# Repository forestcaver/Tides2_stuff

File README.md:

# Tides2_stuff
Panel, modified pcb to put the recom on the back, calibration stuff
(pcb and panel both verified - two modules built 11/4/19)

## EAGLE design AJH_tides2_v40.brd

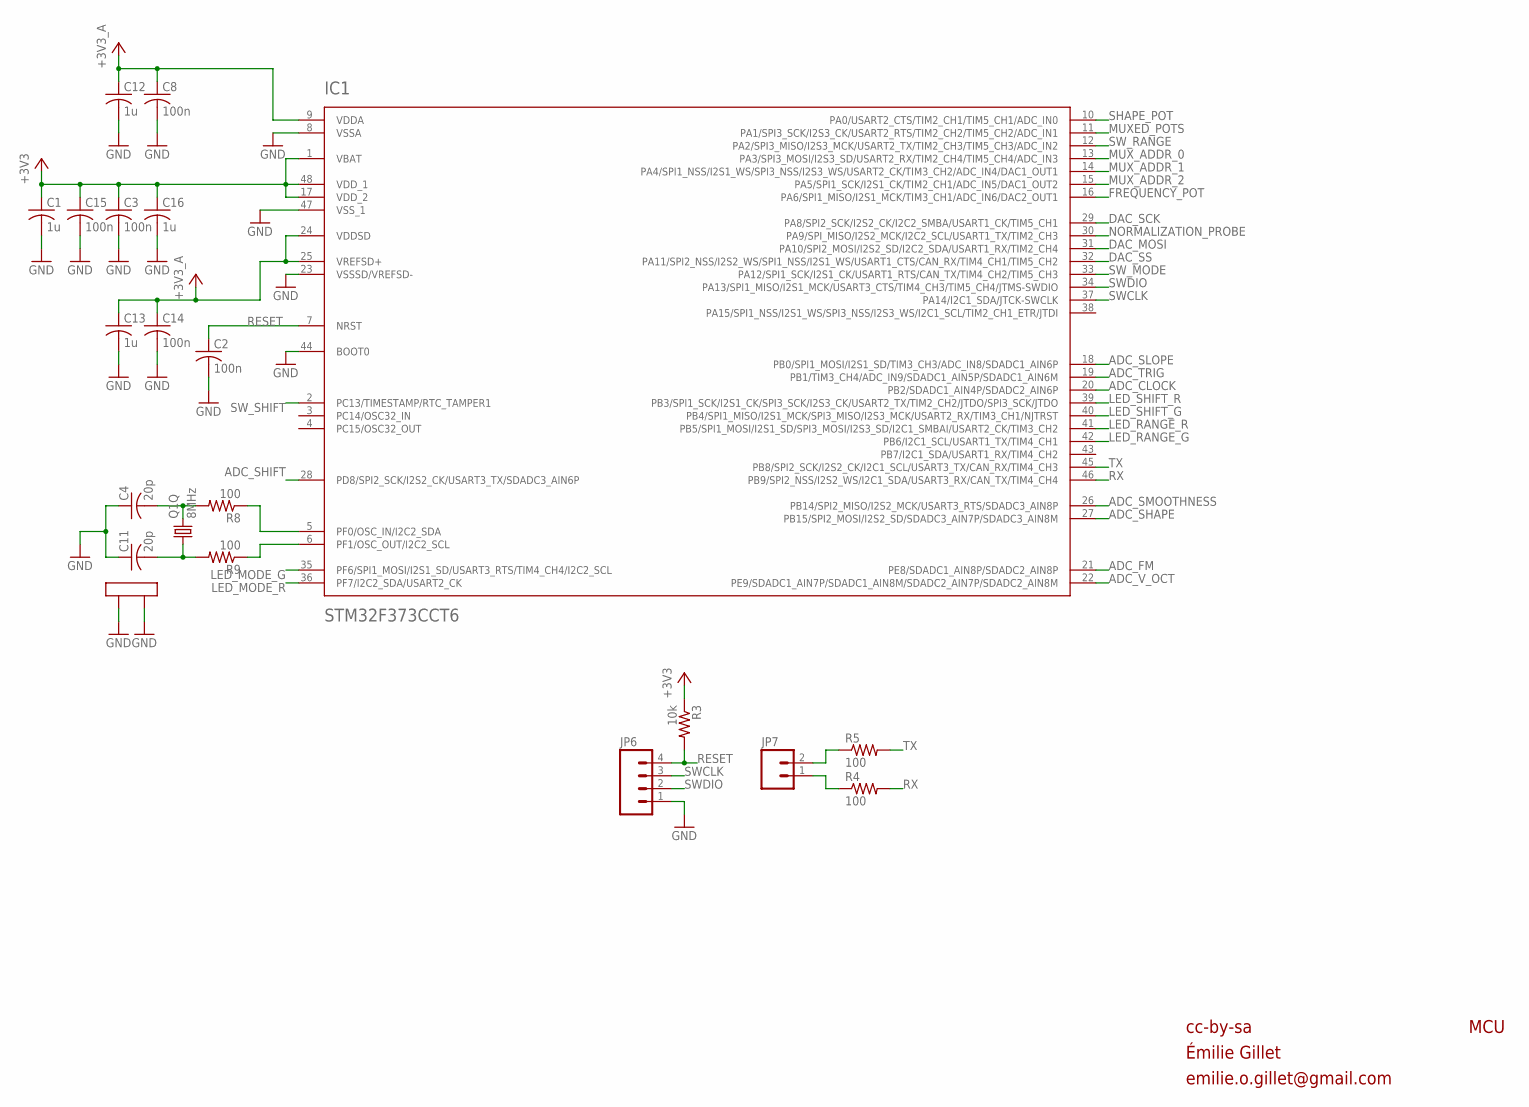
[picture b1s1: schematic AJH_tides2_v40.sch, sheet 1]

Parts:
C1, C12, C13, C16: 1u; C0402
C2, C3, C8, C14, C15: 100n; C0402
C4, C11: 20p; C0402
IC1: STM32F373CCT6; LQFP48
JP6: M04PTH; 1X04
JP7: M02PTH; 1X02
Q1: 8MHz; CTS406
R3: 10k; R0402
R4, R5, R8, R9: 100; R0402

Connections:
+3V3: C1.1, C3.1, C15.1, C16.1, IC1.1 (VBAT), IC1.17 (VDD_2), IC1.48 (VDD_1), R3.1; also elsewhere on the board
+3V3_A: C8.1, C12.1, C13.1, C14.1, IC1.9 (VDDA), IC1.24 (VDDSD), IC1.25 (VREFSD+); also elsewhere on the board
ADC_CLOCK: IC1.20 (PB2/SDADC1_AIN4P/SDADC2_AIN6P); also elsewhere on the board
ADC_FM: IC1.21 (PE8/SDADC1_AIN8P/SDADC2_AIN8P); also elsewhere on the board
ADC_SHAPE: IC1.27 (PB15/SPI2_MOSI/I2S2_SD/SDADC3_AIN7P/SDA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); also elsewhere on the board
ADC_SHIFT: IC1.28 (PD8/SPI2_SCK/I2S2_CK/USART3_TX/SDADC3_A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); also elsewhere on the board
ADC_SLOPE: IC1.18 (PB0/SPI1_MOSI/I2S1_SD/TIM3_CH3/ADC_IN8/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); also elsewhere on the board
ADC_SMOOTHNESS: IC1.26 (PB14/SPI2_MISO/I2S2_MCK/USART3_RTS/SDAD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); also elsewhere on the board
ADC_TRIG: IC1.19 (PB1/TIM3_CH4/ADC_IN9/SDADC1_AIN5P/SDADC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); also elsewhere on the board
ADC_V_OCT: IC1.22 (PE9/SDADC1_AIN7P/SDADC1_AIN8M/SDADC2_AI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); also elsewhere on the board
DAC_MOSI: IC1.31 (PA10/SPI2_MOSI/I2S2_SD/I2C2_SDA/USART1_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); also elsewhere on the board
DAC_SCK: IC1.29 (PA8/SPI2_SCK/I2S2_CK/I2C2_SMBA/USART1_C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); also elsewhere on the board
DAC_SS: IC1.32 (PA11/SPI2_NSS/I2S2_WS/SPI1_NSS/I2S1_WS/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); also elsewhere on the board
FREQUENCY_POT: IC1.16 (PA6/SPI1_MISO/I2S1_MCK/TIM3_CH1/ADC_IN6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); also elsewhere on the board
GND: C1.2, C2.2, C3.2, C4.1, C8.2, C11.1, C12.2, C13.2, C14.2, C15.2, C16.2, IC1.8 (VSSA), IC1.23 (VSSSD/VREFSD-), IC1.44 (BOOT0), IC1.47 (VSS_1), JP6.1, Q1.2 (LID1), Q1.4 (LID2); also elsewhere on the board
LED_MODE_G: IC1.35 (PF6/SPI1_MOSI/I2S1_SD/USART3_RTS/TIM4_C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); also elsewhere on the board
LED_MODE_R: IC1.36 (PF7/I2C2_SDA/USART2_CK); also elsewhere on the board
LED_RANGE_G: IC1.42 (PB6/I2C1_SCL/USART1_TX/TIM4_CH1); also elsewhere on the board
LED_RANGE_R: IC1.41 (PB5/SPI1_MOSI/I2S1_SD/SPI3_MOSI/I2S3_SD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); also elsewhere on the board
LED_SHIFT_G: IC1.40 (PB4/SPI1_MISO/I2S1_MCK/SPI3_MISO/I2S3_M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); also elsewhere on the board
LED_SHIFT_R: IC1.39 (PB3/SPI1_SCK/I2S1_CK/SPI3_SCK/I2S3_CK/U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); also elsewhere on the board
MUXED_POTS: IC1.11 (PA1/SPI3_SCK/I2S3_CK/USART2_RTS/TIM2_CH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); also elsewhere on the board
MUX_ADDR_0: IC1.13 (PA3/SPI3_MOSI/I2S3_SD/USART2_RX/TIM2_CH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); also elsewhere on the board
MUX_ADDR_1: IC1.14 (PA4/SPI1_NSS/I2S1_WS/SPI3_NSS/I2S3_WS/U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); also elsewhere on the board
MUX_ADDR_2: IC1.15 (PA5/SPI1_SCK/I2S1_CK/TIM2_CH1/ADC_IN5/D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); also elsewhere on the board
unnamed: IC1.5 (PF0/OSC_IN/I2C2_SDA), R8.1
unnamed: IC1.6 (PF1/OSC_OUT/I2C2_SCL), R9.1
unnamed: C4.2, Q1.3 (2), R8.2
unnamed: JP7.2, R5.1
unnamed: C11.2, Q1.1, R9.2
unnamed: JP7.1, R4.1
NORMALIZATION_PROBE: IC1.30 (PA9/SPI_MISO/I2S2_MCK/I2C2_SCL/USART1_T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); also elsewhere on the board
RESET: C2.1, IC1.7 (NRST), JP6.4, R3.2
RX: IC1.46 (PB9/SPI2_NSS/I2S2_WS/I2C1_SDA/USART3_RX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), R4.2
SHAPE_POT: IC1.10 (PA0/USART2_CTS/TIM2_CH1/TIM5_CH1/ADC_IN0); also elsewhere on the board
SWCLK: IC1.37 (PA14/I2C1_SDA/JTCK-SWCLK), JP6.3
SWDIO: IC1.34 (PA13/SPI1_MISO/I2S1_MCK/USART3_CTS/TIM4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), JP6.2
SW_MODE: IC1.33 (PA12/SPI1_SCK/I2S1_CK/USART1_RTS/CAN_TX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); also elsewhere on the board
SW_RANGE: IC1.12 (PA2/SPI3_MISO/I2S3_MCK/USART2_TX/TIM2_C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); also elsewhere on the board
SW_SHIFT: IC1.2 (PC13/TIMESTAMP/RTC_TAMPER1); also elsewhere on the board
TX: IC1.45 (PB8/SPI2_SCK/I2S2_CK/I2C1_SCL/USART3_TX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), R5.2

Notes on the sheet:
cc-by-sa
MCU
Émilie Gillet
emilie.o.gillet@gmail.com

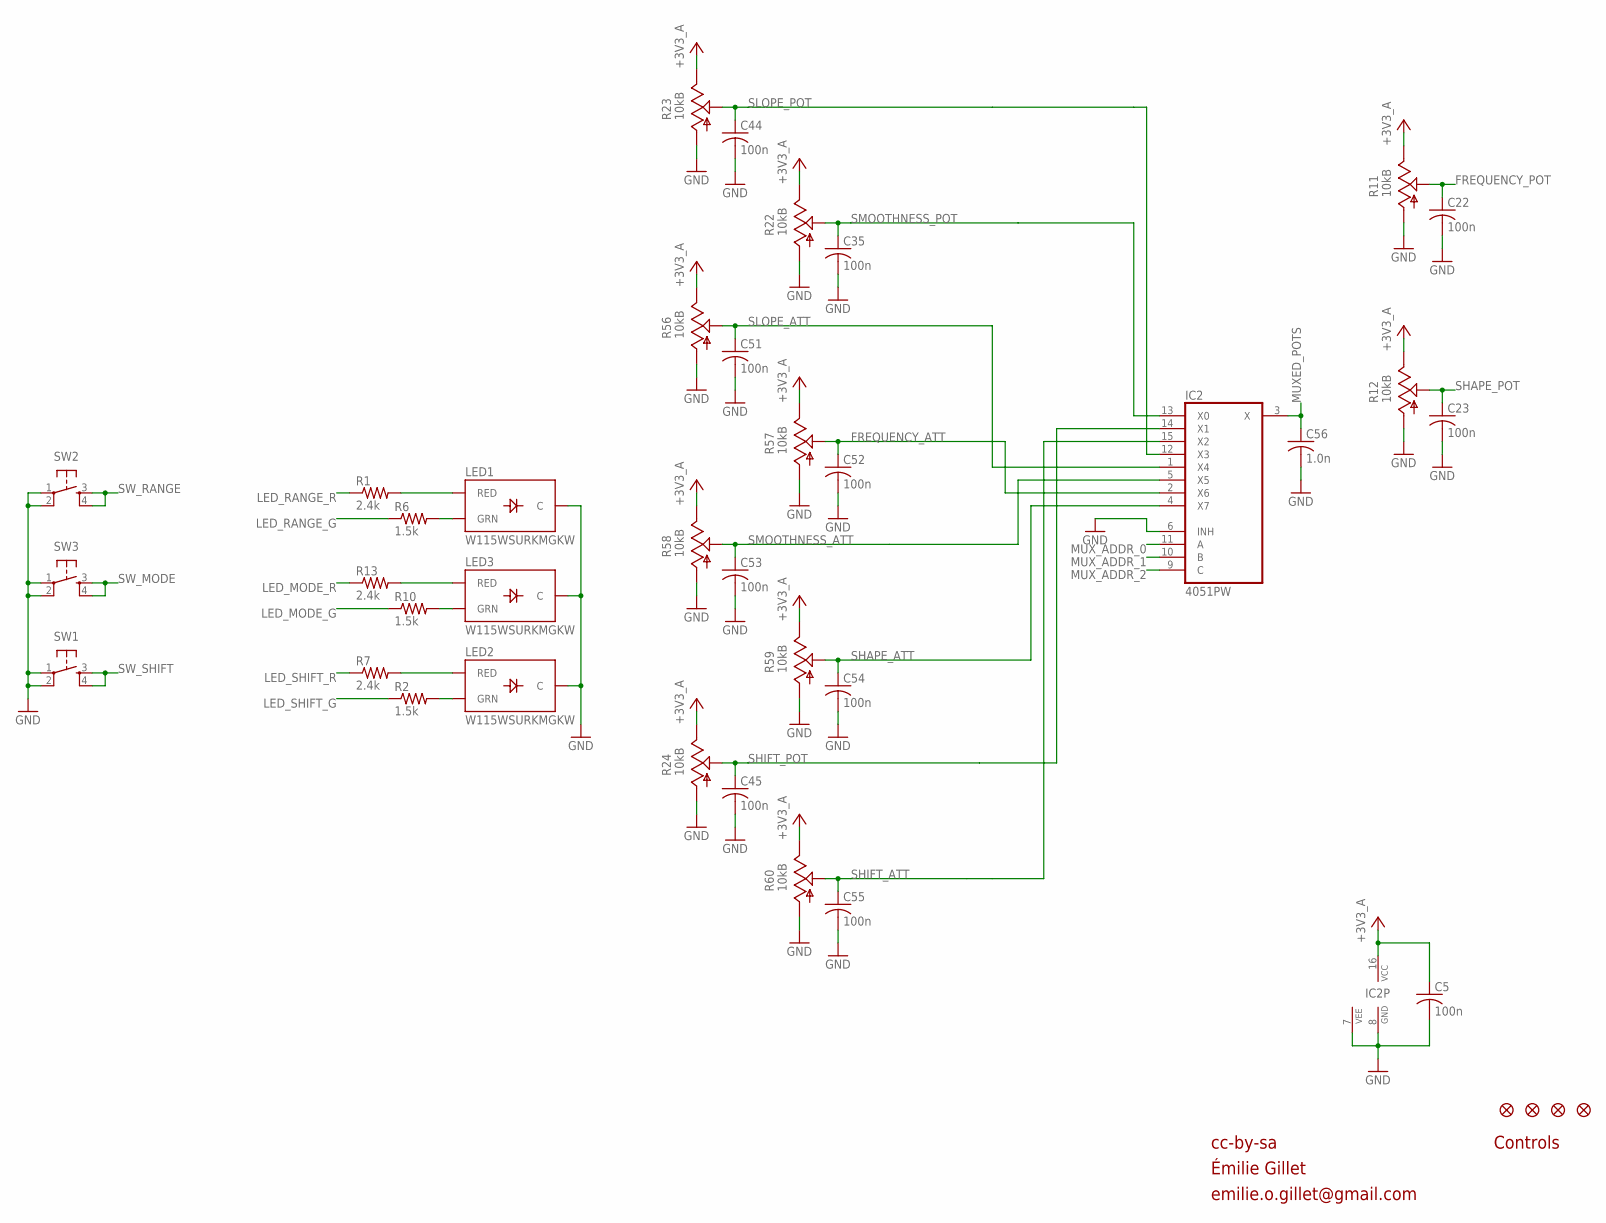
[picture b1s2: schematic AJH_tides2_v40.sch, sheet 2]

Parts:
C5, C22, C23, C35, C44, C45, C51, C52, C53, C54, C55: 100n; C0402
C56: 1.0n; C0402
IC2: 4051PW; TSSOP16_065
JP1, JP2, JP3, JP4: FIDUCIAL1X2; FIDUCIAL-1X2
LED1, LED2, LED3: W115WSURKMGKW; LED-BICOLOR-THROUGHHOLE-2.54
R1, R7, R13: 2.4k; R0402
R2, R6, R10: 1.5k; R0402
R11, R12, R22, R23, R24: 10kB; ALPS_POT_VERTICAL_PS
R56, R57, R58, R59, R60: 10kB; ALPS_POT_VERTICAL
SW1, SW2, SW3: TAC_SWITCHPTH; TACTILE-PTH

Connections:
+3V3_A: C5.1, IC2.16 (VCC), R11.P$1 (E), R12.P$1 (E), R22.P$1 (E), R23.P$1 (E), R24.P$1 (E), R56.P$1 (E), R57.P$1 (E), R58.P$1 (E), R59.P$1 (E), R60.P$1 (E); also elsewhere on the board
FREQUENCY_ATT: C52.1, IC2.2 (X6), R57.P$2 (S)
FREQUENCY_POT: C22.1, R11.P$2 (S); also elsewhere on the board
GND: C5.2, C22.2, C23.2, C35.2, C44.2, C45.2, C51.2, C52.2, C53.2, C54.2, C55.2, C56.2, IC2.6 (INH), IC2.7 (VEE), IC2.8 (GND), LED1.2 (C), LED2.2 (C), LED3.2 (C), R11.P$3 (A), R12.P$3 (A), R22.P$3 (A), R23.P$3 (A), R24.P$3 (A), R56.P$3 (A), R57.P$3 (A), R58.P$3 (A), R59.P$3 (A), R60.P$3 (A), SW1.1, SW1.2, SW2.1, SW2.2, SW3.1, SW3.2; also elsewhere on the board
LED_MODE_G: R10.1; also elsewhere on the board
LED_MODE_R: R13.1; also elsewhere on the board
LED_RANGE_G: R6.1; also elsewhere on the board
LED_RANGE_R: R1.1; also elsewhere on the board
LED_SHIFT_G: R2.1; also elsewhere on the board
LED_SHIFT_R: R7.1; also elsewhere on the board
MUXED_POTS: C56.1, IC2.3 (X); also elsewhere on the board
MUX_ADDR_0: IC2.11 (A); also elsewhere on the board
MUX_ADDR_1: IC2.10 (B); also elsewhere on the board
MUX_ADDR_2: IC2.9 (C); also elsewhere on the board
unnamed: LED1.3 (RED), R1.2
unnamed: LED3.3 (RED), R13.2
unnamed: LED3.1 (GRN), R10.2
unnamed: LED2.3 (RED), R7.2
unnamed: LED1.1 (GRN), R6.2
unnamed: LED2.1 (GRN), R2.2
SHAPE_ATT: C54.1, IC2.4 (X7), R59.P$2 (S)
SHAPE_POT: C23.1, R12.P$2 (S); also elsewhere on the board
SHIFT_ATT: C55.1, IC2.15 (X2), R60.P$2 (S)
SHIFT_POT: C45.1, IC2.14 (X1), R24.P$2 (S)
SLOPE_ATT: C51.1, IC2.1 (X4), R56.P$2 (S)
SLOPE_POT: C44.1, IC2.12 (X3), R23.P$2 (S)
SMOOTHNESS_ATT: C53.1, IC2.5 (X5), R58.P$2 (S)
SMOOTHNESS_POT: C35.1, IC2.13 (X0), R22.P$2 (S)
SW_MODE: SW3.3, SW3.4; also elsewhere on the board
SW_RANGE: SW2.3, SW2.4; also elsewhere on the board
SW_SHIFT: SW1.3, SW1.4; also elsewhere on the board

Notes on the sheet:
cc-by-sa
Controls
Émilie Gillet
emilie.o.gillet@gmail.com

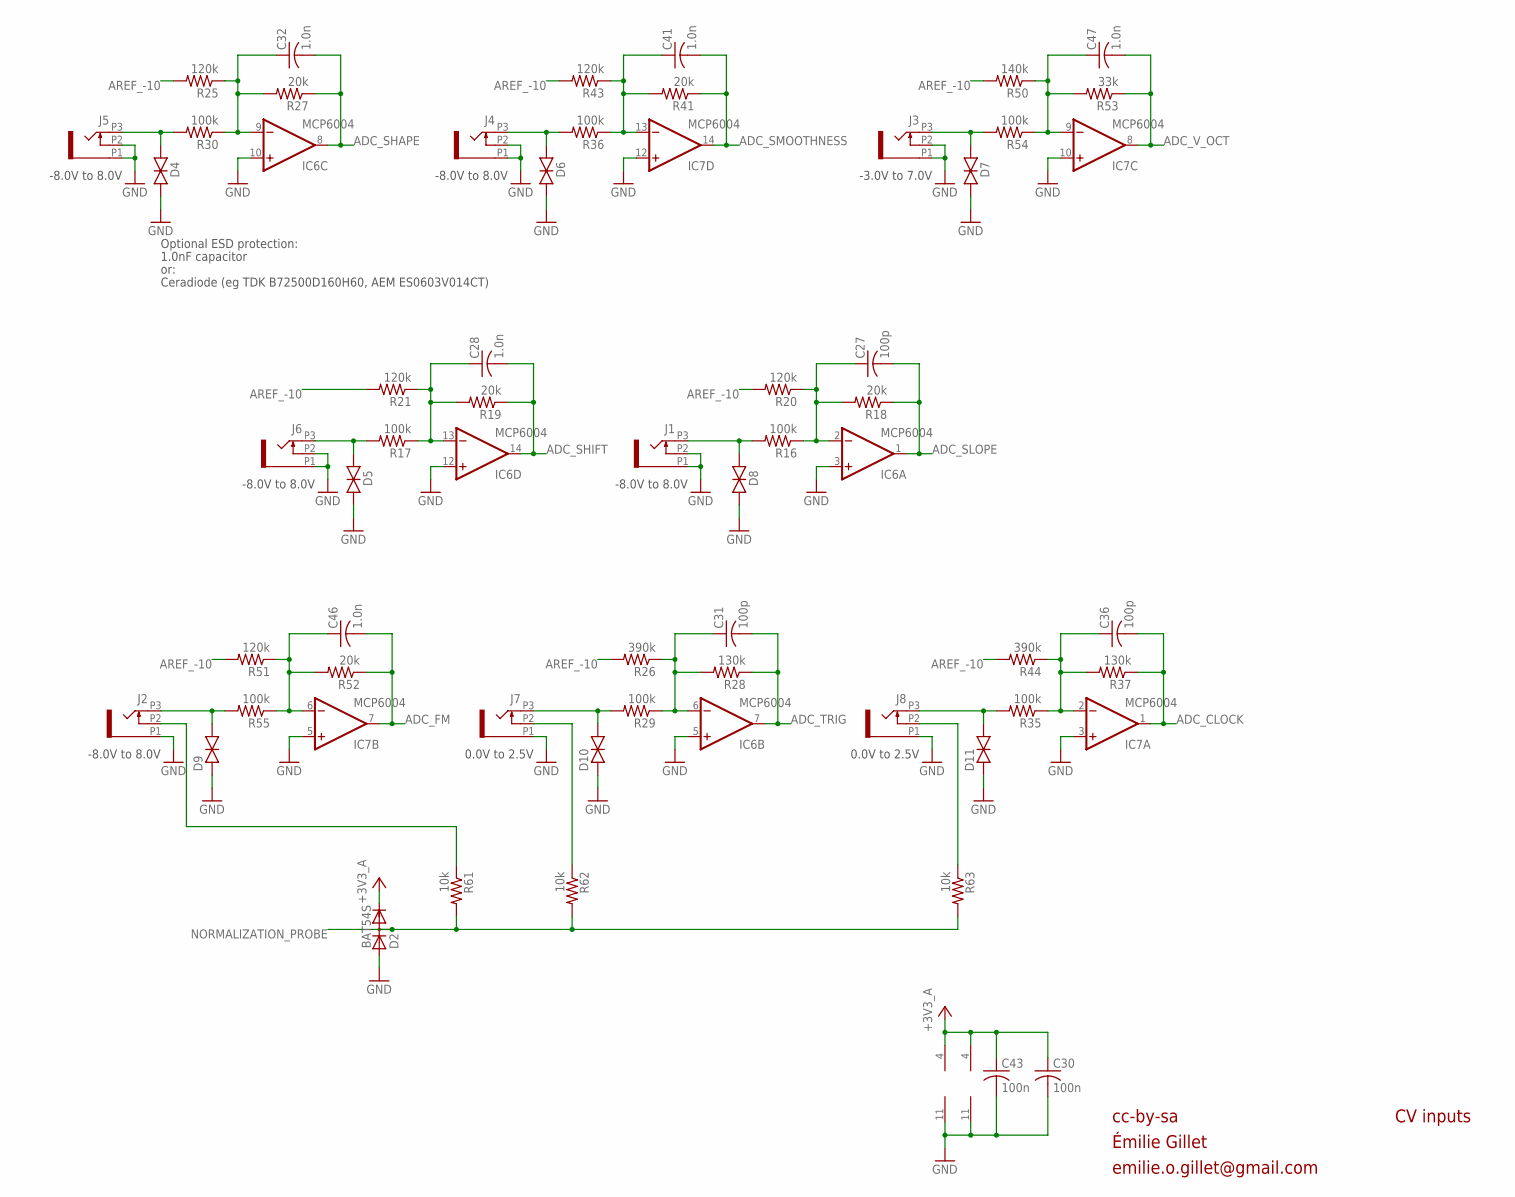
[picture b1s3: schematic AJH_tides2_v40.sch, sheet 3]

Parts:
C27, C31, C36: 100p; C0402
C28, C32, C41, C46, C47: 1.0n; C0402
C30, C43: 100n; C0402
D2: BAT54S; SOT23
D4, D5, D6, D7, D8, D9, D10, D11: TVS; 0603
IC6, IC7: MCP6004; TSSOP14_065
J1, J2, J3, J4, J5, J6, J7, J8: PJ301_THONKICONN6; WQP_PJ_301M6
R16, R17, R29, R30, R35, R36, R54, R55: 100k; R0402
R18, R19, R27, R41, R52: 20k; R0402
R20, R21, R25, R43, R51: 120k; R0402
R26, R44: 390k; R0402
R28, R37: 130k; R0402
R50: 140k; R0402
R53: 33k; R0402
R61, R62, R63: 10k; R0402

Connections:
+3V3_A: C30.1, C43.1, D2.2 (C), IC6.4 (V+), IC7.4 (V+); also elsewhere on the board
ADC_CLOCK: C36.2, IC7.1 (OUT), R37.1; also elsewhere on the board
ADC_FM: C46.2, IC7.7 (OUT), R52.1; also elsewhere on the board
ADC_SHAPE: C32.2, IC6.8 (OUT), R27.1; also elsewhere on the board
ADC_SHIFT: C28.2, IC6.14 (OUT), R19.1; also elsewhere on the board
ADC_SLOPE: C27.2, IC6.1 (OUT), R18.1; also elsewhere on the board
ADC_SMOOTHNESS: C41.2, IC7.14 (OUT), R41.1; also elsewhere on the board
ADC_TRIG: C31.2, IC6.7 (OUT), R28.1; also elsewhere on the board
ADC_V_OCT: C47.2, IC7.8 (OUT), R53.1; also elsewhere on the board
AREF_-10: R20.2, R21.2, R25.2, R26.2, R43.2, R44.2, R50.2, R51.2; also elsewhere on the board
CLOCK_IN: D11.2 (C), J8.P3 (3), R35.2
FM_IN: D9.2 (C), J2.P3 (3), R55.2
GND: C30.2, C43.2, D2.1 (A), D4.1 (A), D5.1 (A), D6.1 (A), D7.1 (A), D8.1 (A), D9.1 (A), D10.1 (A), D11.1 (A), IC6.3 (+IN), IC6.5 (+IN), IC6.10 (+IN), IC6.11 (V-), IC6.12 (+IN), IC7.3 (+IN), IC7.5 (+IN), IC7.10 (+IN), IC7.11 (V-), IC7.12 (+IN), J1.P1 (1), J1.P2 (2), J2.P1 (1), J3.P1 (1), J3.P2 (2), J4.P1 (1), J4.P2 (2), J5.P1 (1), J5.P2 (2), J6.P1 (1), J6.P2 (2), J7.P1 (1), J8.P1 (1); also elsewhere on the board
unnamed: J7.P2 (2), R62.1
unnamed: J8.P2 (2), R63.1
unnamed: C27.1, IC6.2 (-IN), R16.1, R18.2, R20.1
unnamed: J2.P2 (2), R61.1
unnamed: C28.1, IC6.13 (-IN), R17.1, R19.2, R21.1
unnamed: C47.1, IC7.9 (-IN), R50.1, R53.2, R54.1
unnamed: C46.1, IC7.6 (-IN), R51.1, R52.2, R55.1
unnamed: C31.1, IC6.6 (-IN), R26.1, R28.2, R29.1
unnamed: C32.1, IC6.9 (-IN), R25.1, R27.2, R30.1
unnamed: C36.1, IC7.2 (-IN), R35.1, R37.2, R44.1
unnamed: C41.1, IC7.13 (-IN), R36.1, R41.2, R43.1
NORMALIZATION_PROBE: D2.3 (AC), R61.2, R62.2, R63.2; also elsewhere on the board
SHAPE_IN: D4.2 (C), J5.P3 (3), R30.2
SHIFT_IN: D5.2 (C), J6.P3 (3), R17.2
SLOPE_IN: D8.2 (C), J1.P3 (3), R16.2
SMOOTHNESS_IN: D6.2 (C), J4.P3 (3), R36.2
TRIG_IN: D10.2 (C), J7.P3 (3), R29.2
V_OCT_IN: D7.2 (C), J3.P3 (3), R54.2

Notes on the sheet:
cc-by-sa
CV inputs
-8.0V to 8.0V
-3.0V to 7.0V
0.0V to 2.5V
Optional ESD protection:
1.0nF capacitor
or:
Ceradiode (eg TDK B72500D160H60, AEM ES0603V014CT)
Émilie Gillet
emilie.o.gillet@gmail.com

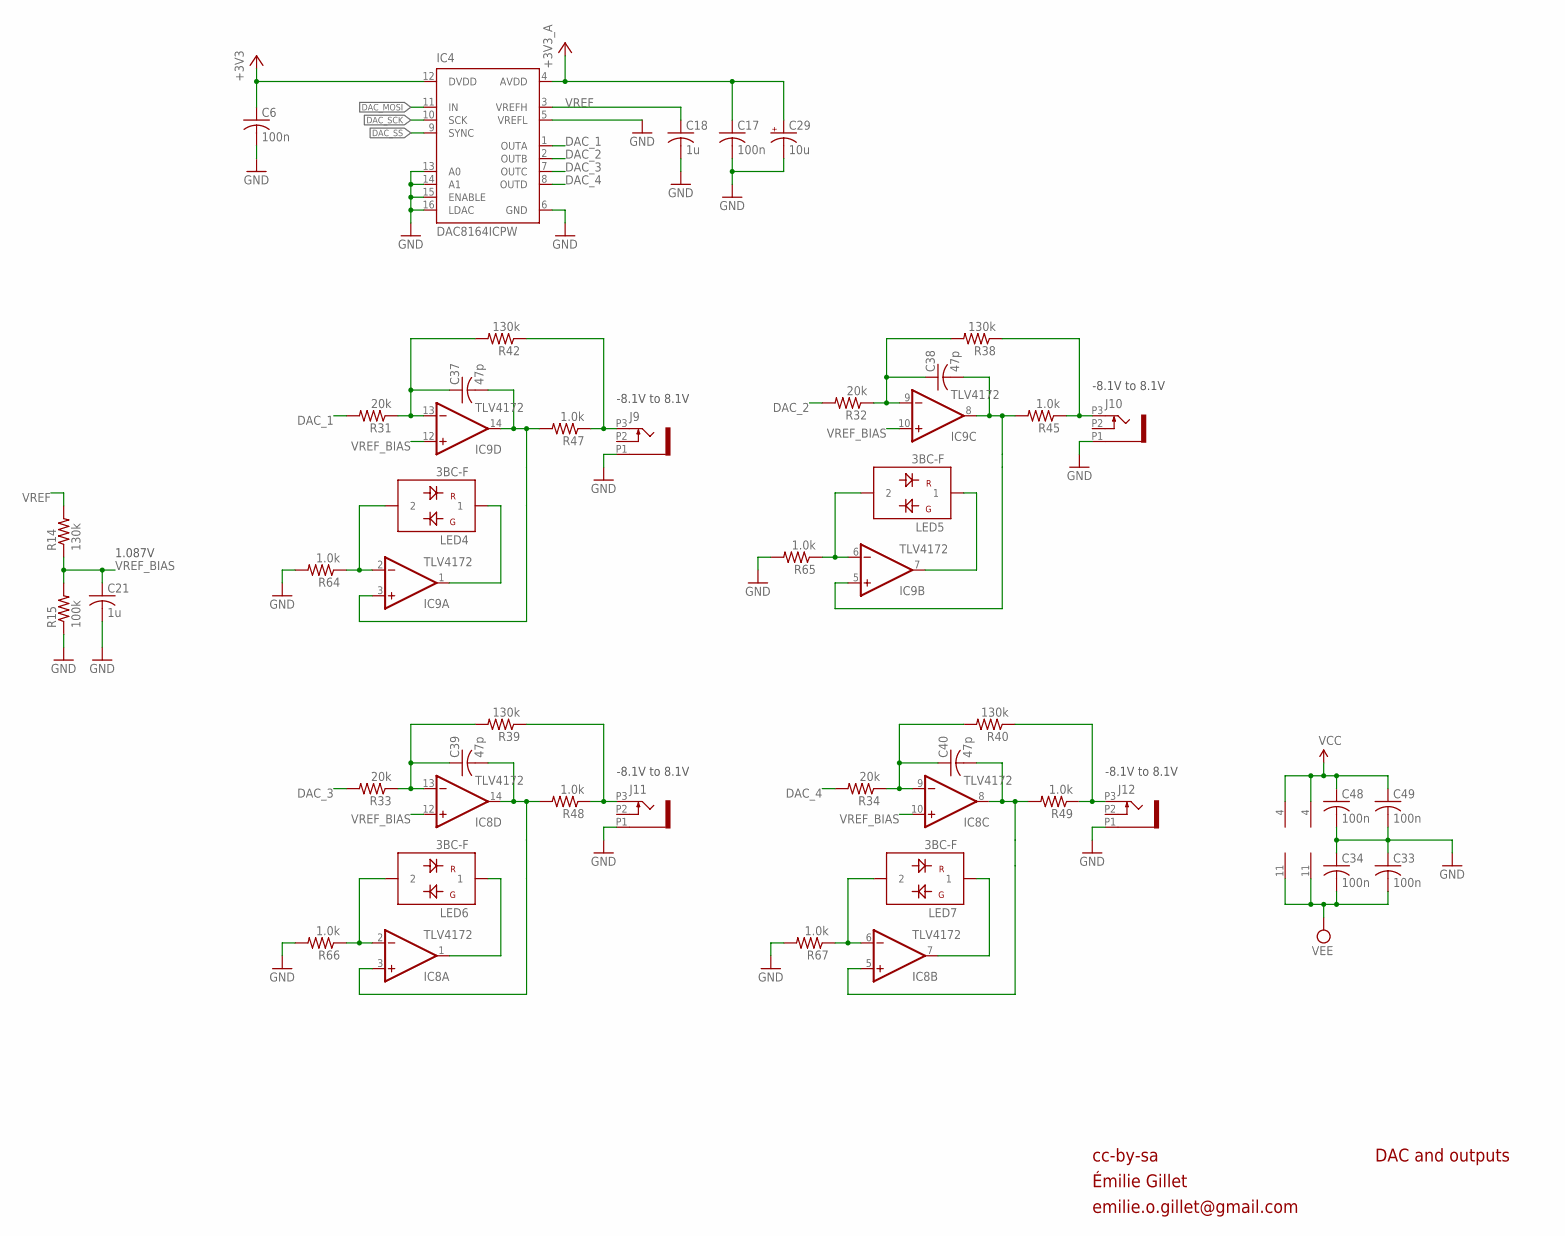
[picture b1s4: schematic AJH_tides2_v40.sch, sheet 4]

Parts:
C6, C17, C33, C34, C48, C49: 100n; C0402
C18, C21: 1u; C0402
C29: 10u; PANASONIC_A
C37, C38, C39, C40: 47p; C0402
IC4: DAC8164ICPW; SOP65P640X110-16N
IC8, IC9: TLV4172; TSSOP14_065
J9, J10, J11, J12: PJ301_THONKICONN6; WQP_PJ_301M6
LED4, LED5, LED6, LED7: 3BC-F; LED3MM
R14, R38, R39, R40, R42: 130k; R0402
R15: 100k; R0402
R31, R32, R33, R34: 20k; R0402
R45, R47, R48, R49: 1.0k; R0603
R64, R65, R66, R67: 1.0k; R0402

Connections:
+3V3: C6.1, IC4.12 (DVDD); also elsewhere on the board
+3V3_A: C17.1, C29.+, IC4.4 (AVDD); also elsewhere on the board
DAC_1: IC4.1 (OUTA), R31.2
DAC_2: IC4.2 (OUTB), R32.2
DAC_3: IC4.7 (OUTC), R33.2
DAC_4: IC4.8 (OUTD), R34.2
DAC_MOSI: IC4.11 (IN); also elsewhere on the board
DAC_SCK: IC4.10 (SCK); also elsewhere on the board
DAC_SS: IC4.9 (SYNC); also elsewhere on the board
GND: C6.2, C17.2, C18.2, C21.2, C29.-, C33.1, C34.1, C48.2, C49.2, IC4.5 (VREFL), IC4.6 (GND), IC4.13 (A0), IC4.14 (A1), IC4.15 (ENABLE), IC4.16 (LDAC), J9.P1 (1), J10.P1 (1), J11.P1 (1), J12.P1 (1), R15.1, R64.2, R65.2, R66.2, R67.2; also elsewhere on the board
unnamed: C37.2, IC9.3 (+IN), IC9.14 (OUT), R47.2
unnamed: J11.P3 (3), R39.1, R48.1
unnamed: J9.P3 (3), R42.1, R47.1
unnamed: C39.1, IC8.13 (-IN), R33.1, R39.2
unnamed: J12.P3 (3), R40.1, R49.1
unnamed: C40.1, IC8.9 (-IN), R34.1, R40.2
unnamed: C38.1, IC9.9 (-IN), R32.1, R38.2
unnamed: C37.1, IC9.13 (-IN), R31.1, R42.2
unnamed: J10.P3 (3), R38.1, R45.1
unnamed: IC9.2 (-IN), LED4.2, R64.1
unnamed: IC9.1 (OUT), LED4.1
unnamed: C38.2, IC9.5 (+IN), IC9.8 (OUT), R45.2
unnamed: IC9.6 (-IN), LED5.2, R65.1
unnamed: IC9.7 (OUT), LED5.1
unnamed: C39.2, IC8.3 (+IN), IC8.14 (OUT), R48.2
unnamed: IC8.2 (-IN), LED6.2, R66.1
unnamed: IC8.1 (OUT), LED6.1
unnamed: C40.2, IC8.5 (+IN), IC8.8 (OUT), R49.2
unnamed: IC8.6 (-IN), LED7.2, R67.1
unnamed: IC8.7 (OUT), LED7.1
VCC: C48.1, C49.1, IC8.4 (V+), IC9.4 (V+); also elsewhere on the board
VEE: C33.2, C34.2, IC8.11 (V-), IC9.11 (V-); also elsewhere on the board
VREF: C18.1, IC4.3 (VREFH), R14.2
VREF_BIAS: C21.1, IC8.10 (+IN), IC8.12 (+IN), IC9.10 (+IN), IC9.12 (+IN), R14.1, R15.2

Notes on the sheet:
cc-by-sa
DAC and outputs
-8.1V to 8.1V
1.087V
Émilie Gillet
emilie.o.gillet@gmail.com

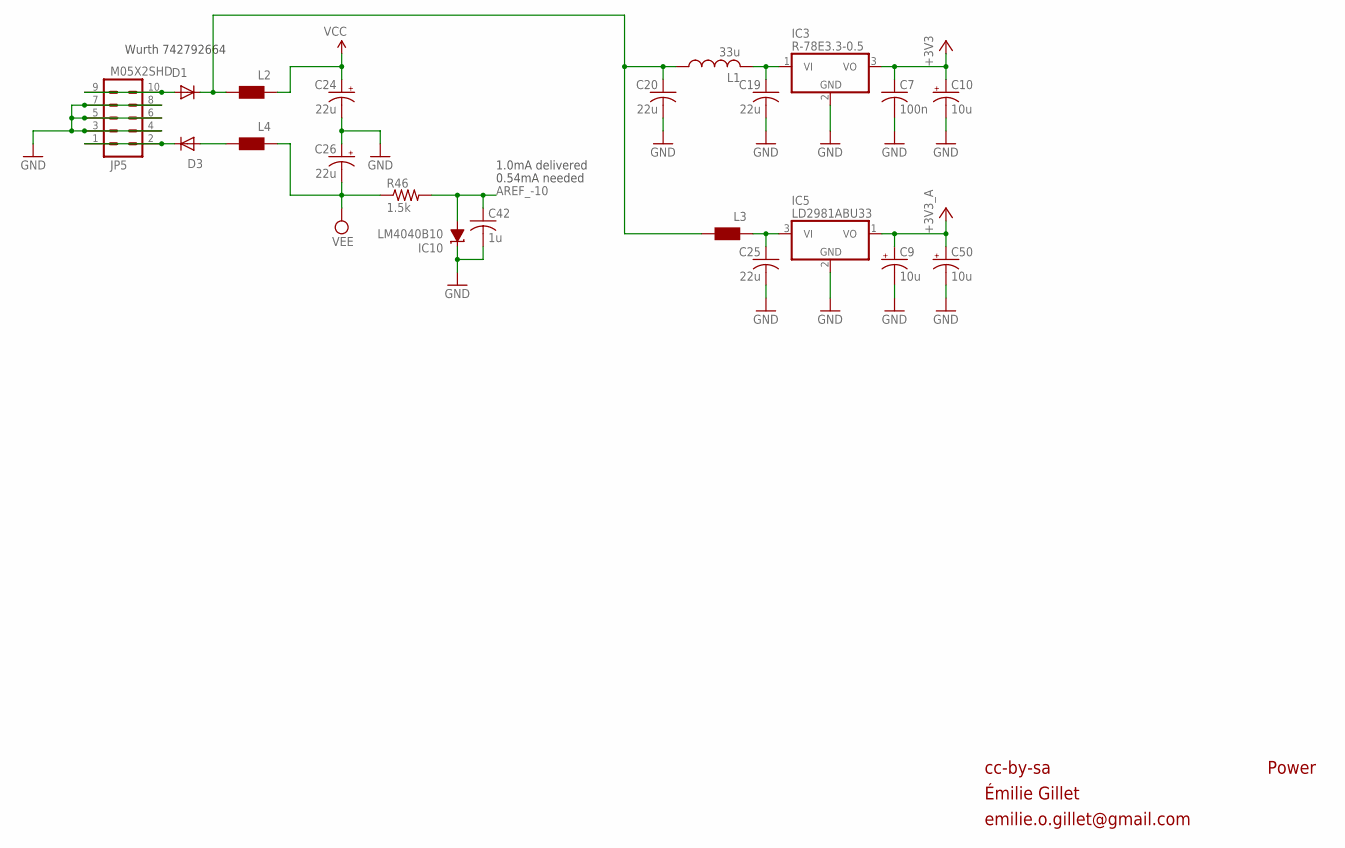
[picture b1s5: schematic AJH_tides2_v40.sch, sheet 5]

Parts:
C7: 100n; C0402
C9, C10, C50: 10u; PANASONIC_A
C19, C20, C25: 22u; C1206
C24, C26: 22u; PANASONIC_B
C42: 1u; C0402
D1, D3: 1N5819HW; SOD123
IC3: R-78E3.3-0.5; WE78
IC5: LD2981ABU33; SOT89
IC10: LM4040B10; DBZ_R-PDSO-G3
JP5: M05X2SHD; 2X5-SHROUDED
L1: 33u; L2012C
L2, L3, L4: WE-CBF_0603; 0603
R46: 1.5k; R0402

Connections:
+3V3: C7.1, C10.+, IC3.3 (VO); also elsewhere on the board
+3V3_A: C9.+, C50.+, IC5.1 (VO); also elsewhere on the board
AREF_-10: C42.1, IC10.2 (A), R46.2; also elsewhere on the board
GND: C7.2, C9.-, C10.-, C19.2, C20.2, C24.-, C25.2, C26.+, C42.2, C50.-, IC3.2 (GND), IC5.2 (GND), IC10.1 (C), JP5.3, JP5.4, JP5.5, JP5.6, JP5.7, JP5.8; also elsewhere on the board
unnamed: C19.1, IC3.1 (VI), L1.2
unnamed: D3.A, L4.2
unnamed: C20.1, D1.C, L1.1, L2.2, L3.2
unnamed: C25.1, IC5.3 (VI), L3.1
unnamed: D1.A, JP5.9, JP5.10
unnamed: D3.C, JP5.1, JP5.2
VCC: C24.+, L2.1; also elsewhere on the board
VEE: C26.-, L4.1, R46.1; also elsewhere on the board

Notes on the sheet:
cc-by-sa
Power
0.54mA needed
Wurth 742792664
1.0mA delivered
Émilie Gillet
emilie.o.gillet@gmail.com

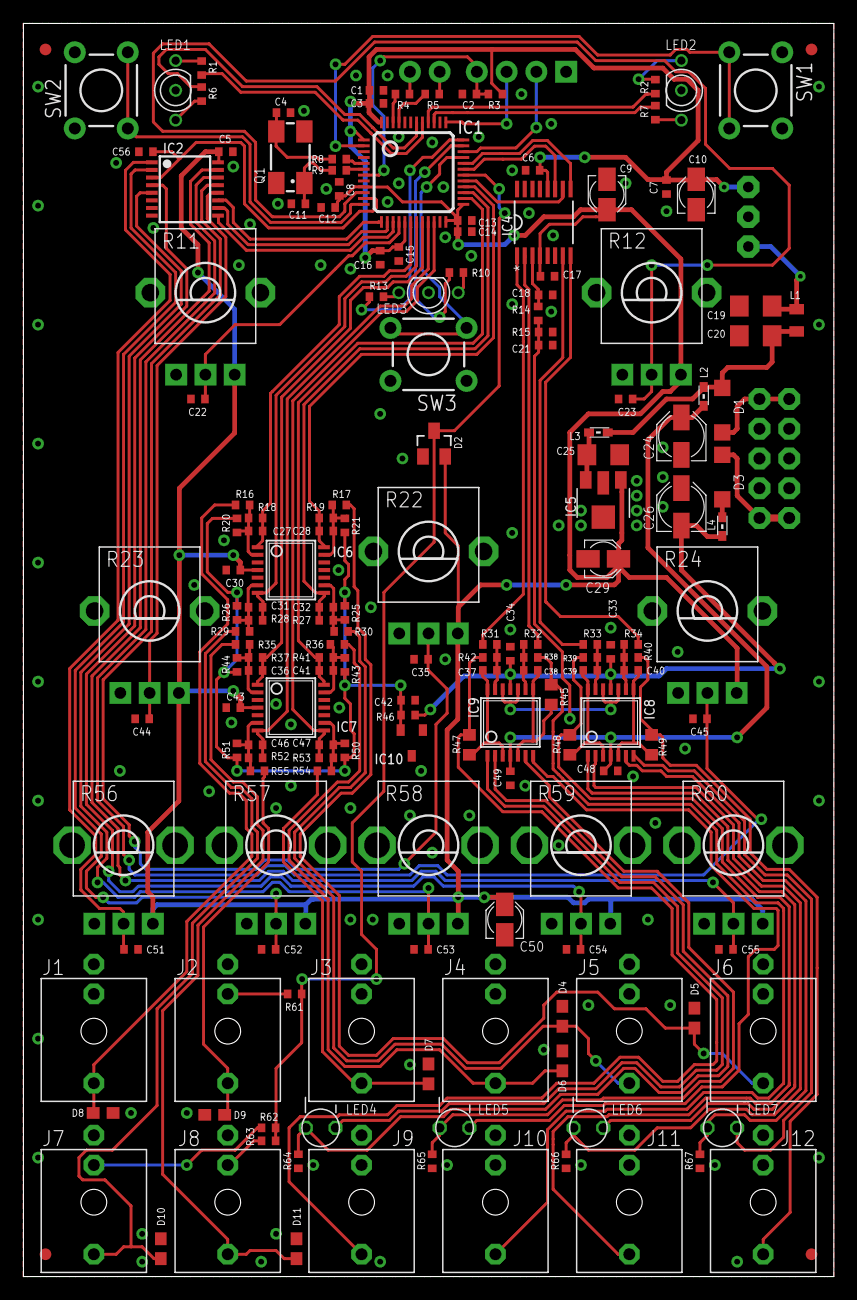
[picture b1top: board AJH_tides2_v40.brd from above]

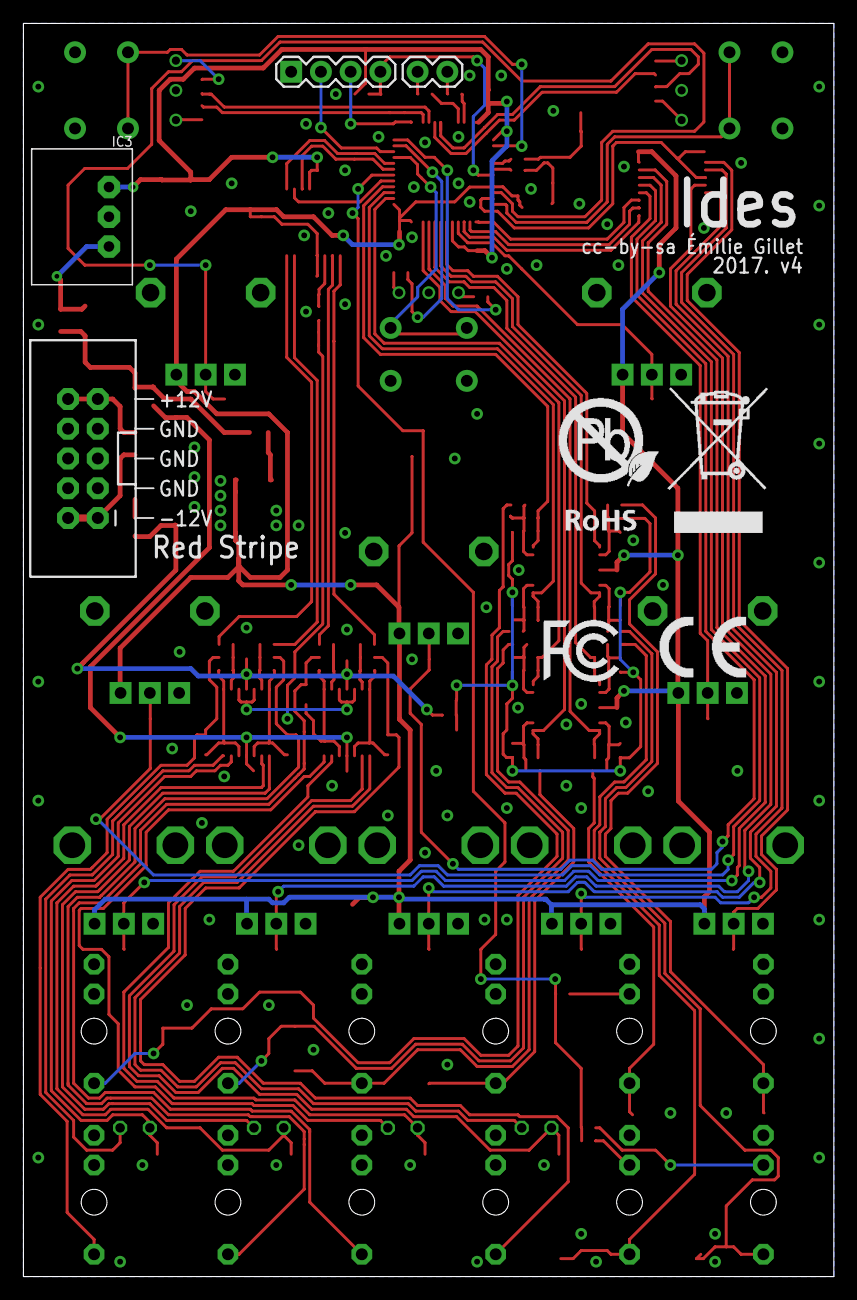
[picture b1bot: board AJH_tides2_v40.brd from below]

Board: 2 copper layers, 69.2 x 107.0 mm, 181 parts (7 on the bottom side), 109 nets.

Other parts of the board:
U$2: ROHS_BIG
U$4: CE_MEDIUM
U$5: FCC_MEDIUM

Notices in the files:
AJH_tides2_v40.brd:
cc-by-sa Émilie Gillet
